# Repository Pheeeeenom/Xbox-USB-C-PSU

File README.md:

# Xbox-USB-C-PSU
The first ever USB C PSU for the original Xbox

# NOTE:
This board currently supports all 3 Xbox motherboard revisions, but requires a different BOM for 009 and 012 than 121.
If you don't know what revision your Xbox is, you can find out with this guide: [https://www.herringhardware.com/xboxrevisions](https://www.herringhardware.com/XboxRevisions.html)

# REPO STRUCTURE:
All source files for the PCB are contained within the respective folder for each of the 3 official Xbox PCB revions,
-121 to start with, and -009 and -012 will be added soon.
Production files to manufacture the PCBs are located in [Releases](https://github.com/Redherring32/Xbox-USB-C-PSU/releases)

# PCB SPECS:
* 4 layers
* 151.739x39.78mm
* 1oz copper (all layers), heat issues may result from skimping on this
* filled vias (VIPPO) for assembly reasons due to via in pad

## LICENSE:
Licensed under
the TAPR Open hardware license (www.tapr.org/OHL)

©Redherring32 2025

## DISCLAIMER:
I offer this with no warranty, express or implied, and I am NOT responsible for anything that may happen as a result of misuse of this PCB.
You have been warned.

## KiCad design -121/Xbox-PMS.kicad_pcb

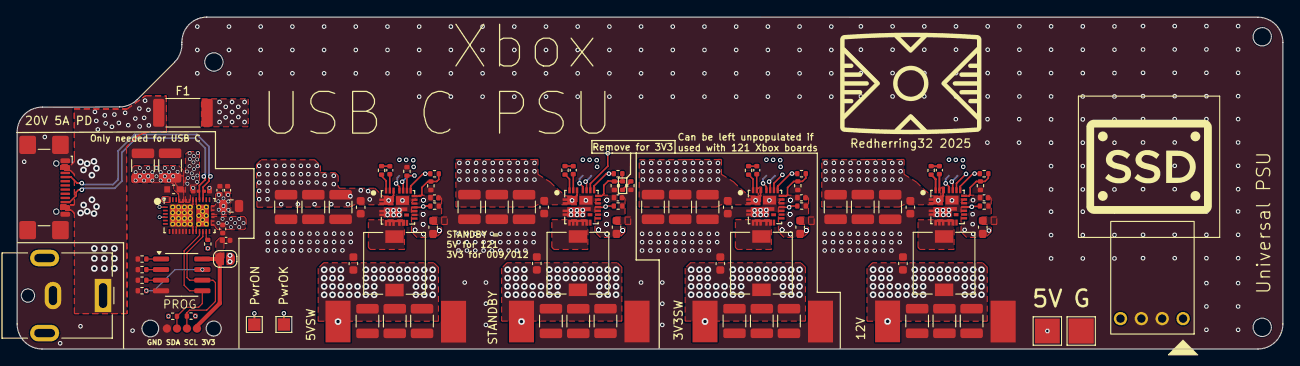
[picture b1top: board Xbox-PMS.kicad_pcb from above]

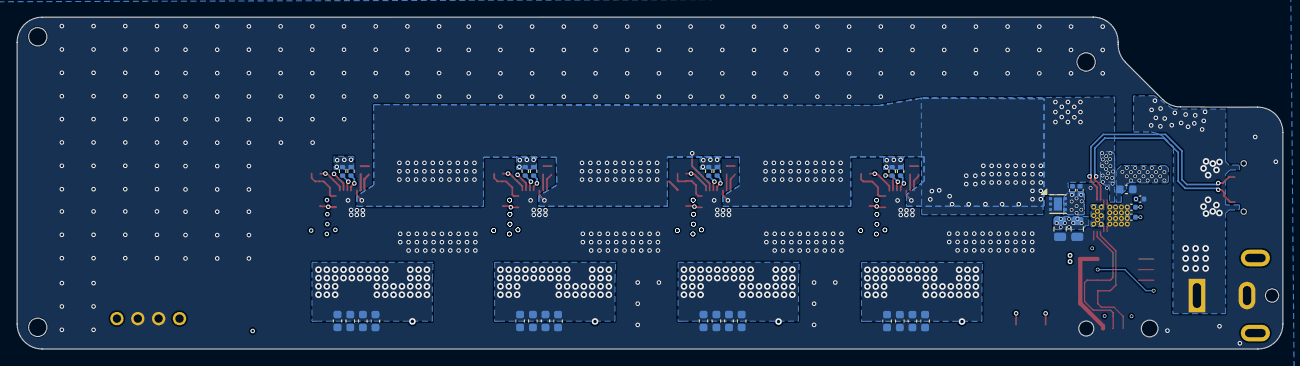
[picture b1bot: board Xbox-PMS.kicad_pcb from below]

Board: 4 copper layers, 151.7 x 39.8 mm, 139 parts (33 on the bottom side), 55 nets.

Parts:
C1, C2, C3, C4, C5, C6, C8, C10, C11, C64, C65, C66: 22uF; C_1210_3225Metric
C7, C9, C13, C30, C31, C33, C34, C35, C36, C37, C38, C39, C40, C41, C44, C67, C74, C75, C76, C77: 22uF; C_0603_1608Metric
C12, C14, C16, C68: 1uF; C_0402_1005Metric
C15, C17, C18, C69: 4.7uF; C_0603_1608Metric
C19, C20, C22, C60, C70: 0.1uF; C_0402_1005Metric
C21, C23, C24, C25, C26, C27, C28, C29, C32, C71, C72, C73: 47uF; C_1210_3225Metric
C42, C43, C45, C78: 0.1uF; C_0603_1608Metric
C46, C49: 100uF 16V; C_1210_3225Metric
C47: 4.7uF 50V; C_0805_2012Metric
C48, C50, C52, C54, C61: 0.1uF 50V; C_0402_1005Metric
C51, C53: 10uF 16V; C_0603_1608Metric
C55, C56, C57: 10uF 16V; C_0402_1005Metric
C58, C59: 22uF 50V; C_0805_2012Metric
C62, C63: 330pF 16V; C_0201_0603Metric
F1: Fuse 5A; Fuse_2512_6332Metric
IC1, IC2, IC3, IC4: SIC437BED-T1-GE3; SIC437BEDT1GE3
J2: USB_C_Receptacle_USB2.0_16P; USB_C_Receptacle_GCT_USB4110
J3: Jack-DC; BarrelJack_CUI_PJ-063AH_Horizontal
J6: Conn_01x04_Pin; PROG
J7: Conn_01x04_Pin; FDD Connector
J8, J9: Conn_01x01_Pin; TestPoint_Pad_1.5x1.5mm
JP1: Jumper_2_Open; SolderJumper-2_P1.3mm_Open_RoundedPad1.0x1.5mm
L1, L3: 780nH; L_7.3x7.3_H4.5
L2, L4: 820nH; L_7.3x7.3_H4.5
R1, R2, R7, R10, R11, R12, R21, R24, R25, R26, R27: 10K; R_0402_1005Metric
R3, R5, R8, R28: 100K; R_0402_1005Metric
R4, R6, R9, R29: 499K; R_0402_1005Metric
R13, R16, R19, R31: 2.2R; R_0402_1005Metric
R14: 45K; R_0402_1005Metric
R15, R18: 4.12K; R_0402_1005Metric
R17, R20: 18.7K; R_0402_1005Metric
R22, R23: 2.2K; R_0402_1005Metric
R30: 430R; R_0402_1005Metric
R32: 8.2K; R_0402_1005Metric
R35: 6.8K; R_0402_1005Metric
R36: 0; R_0402_1005Metric
TP3, TP4, TP5, TP6, TP7, TP8, TP9, TP10: TestPoint; pad
U1: TVS2200DRV; WSON-6-1EP_2x2mm_P0.65mm_EP1x1.6mm
U2: TPS25750; TPS25750D
U3: CAT24C512; SOIC-8_3.9x4.9mm_P1.27mm

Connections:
/3V3: C57.1, U2.38 (VIN_3V3)
/3V3SB: C23.2, C25.1, C28.1, C31.1, C34.1, C37.1, C40.1, C43.1, IC1.18 (VOUT), L2.2, R17.1, TP5.1
/3V3SW: C21.2, C24.1, C27.1, C30.1, C33.1, C36.1, C39.1, C42.1, IC2.18 (VOUT), L1.2, R14.1, TP3.1
/5VSW: C26.2, C29.1, C32.1, C35.1, C38.1, C41.1, C44.1, C45.1, IC3.18 (VOUT), J7.4, L3.2, R20.1, TP7.1
/12V: C71.2, C72.1, C73.1, C74.1, C75.1, C76.1, C77.1, C78.1, IC4.18 (VOUT), J7.1, L4.2, R32.1, TP9.1
/CCx+: C63.1, J2.A5 (CC1), U2.28 (CC1)
/CCx-: C62.1, J2.B5 (CC2), U2.29 (CC2)
/DRAIN: U2.15 (DRAIN), U2.30 (DRAIN), U2.40 (DRAIN_PAD)
/EEPROM_3V3: C60.1, J6.4, JP1.1 (A), U3.8 (VCC)
/EN: IC2.19 (EN), IC3.19 (EN), IC4.19 (EN), J9.1, R11.1
/LDO_1V5: C56.1, U2.4 (LDO_1V5)
/LDO_3V3: C55.1, JP1.2 (B), R21.2, R22.2, R23.2, U2.1 (LDO_3V3)
/PGOOD: IC1.14 (P_GOOD), IC2.14 (P_GOOD), IC3.14 (P_GOOD), IC4.14 (P_GOOD), J8.1, R1.1, R2.1, R7.1, R10.1
/PP5V: C46.1, C49.1, C51.1, C53.1, U2.34 (PP5V), U2.35 (PP5V)
/PPHV: C58.1, C59.1, C61.1, U2.20 (PPHV), U2.21 (PPHV), U2.22 (PPHV)
/SCL: J6.3, R23.1, U2.17 (I2Cm_SCL), U3.6 (SCL)
/SDA: J6.2, R22.1, U2.16 (I2Cm_SDA), U3.5 (SDA)
/VBUS-IN: F1.1, J2.A4 (VBUS), J2.A9 (VBUS), J2.B4 (VBUS), J2.B9 (VBUS), J3.1
/VBUS-SAFE: C1.1, C2.1, C3.1, C4.1, C5.1, C6.1, C7.1, C8.1, C9.1, C10.1, C11.1, C13.1, C47.1, C48.1, C50.1, C52.1, C54.1, C64.1, C65.1, C66.1, C67.1, F1.2, IC1.1 (VIN), IC1.2 (VIN), IC1.19 (EN), IC1.22 (VIN), IC1.26 (VIN), IC2.1 (VIN), IC2.2 (VIN), IC2.22 (VIN), IC2.26 (VIN), IC3.1 (VIN), IC3.2 (VIN), IC3.22 (VIN), IC3.26 (VIN), IC4.1 (VIN), IC4.2 (VIN), IC4.22 (VIN), IC4.26 (VIN), U1.4 (IN), U1.5 (IN), U1.6 (IN), U2.23 (VBUS_IN), U2.24 (VBUS_IN), U2.25 (VBUS_IN), U2.32 (VBUS), U2.33 (VBUS)
/VDD: C12.2, C14.2, C15.2, C16.2, C17.2, C18.2, C68.2, C69.2, IC1.12 (V_DRV), IC1.15 (VDD), IC2.12 (V_DRV), IC2.15 (VDD), IC3.12 (V_DRV), IC3.15 (VDD), IC4.12 (V_DRV), IC4.15 (VDD), R1.2, R2.2, R3.2, R4.1, R5.2, R6.1, R7.2, R8.2, R9.1, R10.2, R28.2, R29.1
/~IRQ: R21.1, U2.18 (I2Cm_IRQ_N)
GND: C1.2, C2.2, C3.2, C4.2, C5.2, C6.2, C7.2, C8.2, C9.2, C10.2, C11.2, C12.1, C13.2, C14.1, C15.1, C16.1, C17.1, C18.1, C21.1, C23.1, C24.2, C25.2, C26.1, C27.2, C28.2, C29.2, C30.2, C31.2, C32.2, C33.2, C34.2, C35.2, C36.2, C37.2, C38.2, C39.2, C40.2, C41.2, C42.2, C43.2, C44.2, C45.2, C46.2, C47.2, C48.2, C49.2, C50.2, C51.2, C52.2, C53.2, C54.2, C55.2, C56.2, C57.2, C58.2, C59.2, C60.2, C61.2, C62.2, C63.2, C64.2, C65.2, C66.2, C67.2, C68.1, C69.1, C71.1, C72.2, C73.2, C74.2, C75.2, C76.2, C77.2, C78.2, IC1.3 (PGND), IC1.4 (PGND), IC1.13 (PGND), IC1.16 (AGND), IC1.25 (AGND), IC1.27 (PGND), IC1.29 (PGND), IC2.3 (PGND), IC2.4 (PGND), IC2.13 (PGND), IC2.16 (AGND), IC2.25 (AGND), IC2.27 (PGND), IC2.29 (PGND), IC3.3 (PGND), IC3.4 (PGND), IC3.13 (PGND), IC3.16 (AGND), IC3.25 (AGND), IC3.27 (PGND), IC3.29 (PGND), IC4.3 (PGND), IC4.4 (PGND), IC4.13 (PGND), IC4.16 (AGND), IC4.25 (AGND), IC4.27 (PGND), IC4.29 (PGND), J2.A1 (GND), J2.A12 (GND), J2.B1 (GND), J2.B12 (GND), J2.S1 (SHIELD), J3.2, J6.1, J7.2, J7.3, R11.2, R12.2, R15.2, R18.2, R24.2, R25.2, R26.2, R27.2, R30.2, R35.2, TP4.1, TP6.1, TP8.1, TP10.1, U1.1 (GND), U1.2 (GND), U1.3 (GND), U1.7 (GND), U2.8 (I2Cs_SDA), U2.9 (I2Cs_SCL), U2.10 (I2Cs_IRQ_N), U2.11 (GND), U2.12 (GND), U2.14 (GND), U2.31 (GND), U2.39 (GND_PAD), U3.4 (GND)
unnamed: C19.2, R13.2
unnamed: C20.2, R16.2
unnamed: C22.2, R19.2
unnamed: C70.2, R31.2
unnamed: C20.1, IC1.23 (BOOT)
unnamed: IC1.17 (FB), R15.1, R17.2
unnamed: IC1.21 (MODE1), R5.1
unnamed: IC1.20 (MODE2), R6.2
unnamed: IC1.24 (PHASE), R16.1
unnamed: IC1.5 (SW), IC1.6 (SW), IC1.7 (SW), IC1.8 (SW), IC1.9 (SW), IC1.30 (SW), L2.1
unnamed: C19.1, IC2.23 (BOOT)
unnamed: IC2.17 (FB), R12.1, R14.2
unnamed: IC2.21 (MODE1), R3.1
unnamed: IC2.20 (MODE2), R4.2
unnamed: IC2.24 (PHASE), R13.1
unnamed: IC2.5 (SW), IC2.6 (SW), IC2.7 (SW), IC2.8 (SW), IC2.9 (SW), IC2.30 (SW), L1.1
unnamed: C22.1, IC3.23 (BOOT)
unnamed: IC3.17 (FB), R18.1, R20.2, R36.1
unnamed: IC3.21 (MODE1), R8.1
unnamed: IC3.20 (MODE2), R9.2
unnamed: IC3.24 (PHASE), R19.1
unnamed: IC3.5 (SW), IC3.6 (SW), IC3.7 (SW), IC3.8 (SW), IC3.9 (SW), IC3.30 (SW), L3.1
unnamed: C70.1, IC4.23 (BOOT)
unnamed: IC4.17 (FB), R30.1, R32.2
unnamed: IC4.21 (MODE1), R28.1
unnamed: IC4.20 (MODE2), R29.2
unnamed: IC4.24 (PHASE), R31.1
unnamed: IC4.5 (SW), IC4.6 (SW), IC4.7 (SW), IC4.8 (SW), IC4.9 (SW), IC4.30 (SW), L4.1
unnamed: R35.1, R36.2
unnamed: R24.1, U3.1 (A0)
unnamed: R25.1, U3.2 (A1)
unnamed: R26.1, U3.3 (A2)
unnamed: R27.1, U3.7 (WP)

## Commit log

2025-04-14 Add -121 Files
2025-04-15 Update README.md
    Update Readme
2025-04-15 Update README.md
    Fix Hyperlink
2025-04-15 Update README.md
    Fix typo
2025-04-15 Add LICENSE Add CONTRIB.txt
2025-04-15 * Enlarge Pin 1 markers * Clean up zone outlines
2025-05-21 + Update design to Universal, 1 PCB covers all 3 Xbox Motherboard Revisions now. + Clean up schematic refdes + Clean up zone outlines + Add 009/012 schematic
2025-05-21 Update PCB image, Update PCB dimensions.
2025-05-21 Edit NOTE: to reflect new version
2025-07-05 Fix value of R15 in -009_012 schematic
2025-07-06 Add jumper 0ohm
    configurable STANDBY voltage.
    update silkscreen
